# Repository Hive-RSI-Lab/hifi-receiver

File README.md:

# hifi-receiver-2

The WiiM-Ultra-like hi-fi streaming receiver/amp product in tiers (barebones, medium, full), designed with hwde on H0: boards, firmware, app, enclosure, manuals.

- [docs/product.md](docs/product.md): the three tiers (Lite, Plus, Ultra), every decision and why, power, cost and build order.
- [docs/plan.md](docs/plan.md): the later work in order, one worker session each.
- [docs/bom-estimate.csv](docs/bom-estimate.csv) + `python3 tools/bom_estimate.py`: per-tier BOM and JLC cost at 10 and 100 units (`--unit lite 100` prints one number).
- [docs/bom-stock.md](docs/bom-stock.md) + `python3 tools/bom_stock.py`: every board's BOM against live JLC and LCSC stock before an order, with checked alternates ([bom-alternates.csv](docs/bom-alternates.csv)) where a part is short.
- [docs/checks.md](docs/checks.md) + `python3 tools/hwcheck.py test|score`: the project's check (product.md complete, every board passes hwde's erc, drc_routed, verify and dfm gates) and score (the whole product, lower is better: every tier's unit cost at 100 from its boards' BOMs, counted only when they pass their gates and carry every function [`tools/product.json`](tools/product.json) names, plus 100 for each piece (firmware, app, bench, enclosures, manual) until its check in `tools/pieces.py`, which a stub fails, and its tests pass).
- [docs/order-readiness.md](docs/order-readiness.md): where each board stands before the order (gates, sims, reviews, firmware, bring-up plans) and what needs the person.
- [docs/manual/](docs/manual/user-manual.md): the user manual for all three tiers, the one-page [quick start](docs/manual/quick-start.md) for the box, and [sources.md](docs/manual/sources.md): where each fact comes from and what is still to be confirmed.
- [docs/app.md](docs/app.md) + `app/`: the web app (PWA) the firmware serves: what it does, the API it needs beyond docs/test-api.md, a mock receiver (`python3 app/mock/server.py`), the firmware pack (`python3 app/build.py`), tests (`python3 app/tests/test_app.py`) and screenshots.

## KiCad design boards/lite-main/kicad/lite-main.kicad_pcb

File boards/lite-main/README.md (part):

# lite-main: the Lite tier of hifi-receiver-2

The Lite tier's one board, as `docs/product.md` defines it. You plug a USB-C PD
laptop charger of 65 W or more and a pair of speakers into it (Lite asks for
20 V and uses at most what that contract allows, 60–65 W with an ordinary
cable: a bigger charger adds nothing; see issue #136). It streams over Wi-Fi
(Spotify Connect, AirPlay, Lyrion) and Bluetooth, takes a DJ deck on RCA, and
drives two subwoofers from RCA sub outs. A web app on your phone, three buttons
or any IR remote control it.

It was designed with the hive-hwde module (KiCad 10), from schematic to JLC fab
package, on 2026-10-28. **Nothing has been ordered.** Ordering and paying are
the person's. The workspace is named after the board, `boards/lite-main/` (the
brief said `boards/lite/`): that is the path `tools/hwcheck.py` scores, from
product.md's Boards row.

## What it is

- **Board:** 2 layers, 1.6 mm FR-4, 1 oz, OSP, 118 x 90 mm, four M3 holes
  (H1-H3 plated, H4 bare), 2 mm corners. 154 parts, all on the top side. 147 are SMT; 7 are
  through-hole (J2, J3, J4-J7 and U9). The 4 mounting holes are not BOM parts.
  JLC assembly with LCSC part numbers.
- **Rear edge, left to right:**
  - **J2:** RCA line in (FLX4). Top jack white = L, bottom red = R. ESD: D3/D4.
  - **J3:** RCA sub out L/R. ESD: D5/D6.
  - **J1:** USB-C.
  - **J4-J7:** the speaker outputs, four 4 mm banana sockets (Amass 24.243,
    right-angle PCB mount, 24 A, red C7437321 / black C7437322; JLC fits
    them): J4 L+, J5 L-, J6 R+, J7 R-, at 11 mm pitch. Their round collars
    (9.40 mm across, 2.60 mm long, bottom 3.20 mm over the board) reach 2.65 mm
    past the rear edge into the enclosure's 10.2 mm round holes, bore axis
    8.1 mm over the board. Body 10.10 mm wide, 10.70 mm across the rib; pins
    15.5 +/-0.3 mm (Multicomp's sheet for the same part numbers; Amass's says 15.7). Nothing is wired by hand. Single banana plugs;
    the 11 mm pitch is too close for a dual (19 mm) plug.
- **Front edge:** SW1 vol-, SW2 vol+, SW3 play/source (hold = BT pairing),
  the IR receiver U9 (an IRM-3638T standing at the edge with its lens facing
  forward through the front wall) and a red status LED D2.
- **ESP32 antenna:** at the left edge. A copper keep-out on both layers runs
  from 15 mm above it to the bottom edge, and no copper is left in the check's
  15 mm bands either side. H4, 8 mm below the antenna, is a bare unplated hole
  for that reason, so a metal screw there sits near the antenna with no ground
  bond (`docs/boards/lite-preorder.md`).

| Block | Parts | Notes |
|---|---|---|
| USB-C + PD | J1 HRO TYPE-C-31-M-12 (20 V/5 A), U1 CH224A, D1 SMBJ22A; ESD: D7/D8 PESDNC2FD5VB (D+/D-; CC exempt, docs/boards/lite-esd.md) | asks for 20 V (Rset 120k); I2C 0x22 on the codec's bus, so firmware reads the protocol status (0x09) and the PDO's max current (0x50). The CH224A has no SRCCAP registers (CH224Q only). |
| PVDD switch | Q1 AO4485, Q4 MMBT3904 | on only when GPIO18 is high **and** the PD contract is good (Q4's emitter is CH224A PG); C19 holds the gate shut on VBUS steps; soft start ~28 ms, 0.41 A inrush; R16 bleeder |
| 5 V | U2 TPS54302, L5 10 uH | TI design-example values |
| 3.3 V | U3 SY8089 (digital), U4 LP5907 (codec analog) | |
| MCU | U5 ESP32-WROVER-E-N8R8, U6 CH340B, Q2/Q3 | console + flashing over the same USB-C; auto-program on DTR/RTS |
| Codec | U7 ES8388 | pinned like the ESP32-A1S AudioKit (I2S MCLK 0, BCLK 27, LRCK 25, DOUT 26, DIN 35; I2C 32/33): squeezelite-esp32's board profile applies |
| Amp | U8 TPA3118D2, L1-L4 10 uH 8 A, C68-C71 1 uF | BTL, 26 dB, BD mode, no power limit; 2 x 38.7 W into 4 ohm at 20 V, 1 % THD (review-2) |
| Self-measurement | R66-R69, C81-C84 | SPK_L_P / SPK_R_P through 100k/10k, 470 pF, 1 uF into the codec's LIN2/RIN2: the board records its own speaker outputs (ratio 0.0625 with the ADC's input) |
| Bulk | C58 470 uF polymer, C59 220 uF | |

ESP32 pin map:

| GPIO | Signal |
|---|---|
| 0 | MCLK |
| 4 | PD power-good |
| 13 | vol+ |
| 14 | IR |
| 18 | PVDD enable |
| 19 | play |
| 21 | amp SDZ (through 100k) |
| 22 | LED |
| 23 | amp fault |
| 34 | VBUS/11 |
| 39 | PVDD/11 (firmware confirms the switch closed) |
| 36 | vol- |
| 1/3 | UART0, also on spare header J8 |
| 5, 15 | unused by the audio side, on spare header J8 (boot straps) |

The full table is in [`architecture/blocks.md`](architecture/blocks.md). Spare header J8:
[`docs/boards/lite-header.md`](../../docs/boards/lite-header.md).

## First-spin review (review-2, 2026-10-29)

Six independent reviewers (power, audio, digital/RF, thermal, DFM, parts
pin-to-pad) read this board from its KiCad files and the vendor datasheets:
[`docs/review-2/`](../../docs/review-2/). No pinout errors. What changed on
this board because of it:

| Finding | Was | Now |
|---|---|---|
| AUDIO-4 / DIGITAL-14 (major): the amp could stay in shutdown, since SDZ's up-to-50 uA input current through 100k left it under 2 V | R54 100k | R54 10k (SDZ >= 2.7 V) + C26 47 nF slew limit |
| POWER-3 (major): Q1 turned itself on at every VBUS step with the firmware off (C2 Miller coupling) | R6 47k | R6 220k + C19 4.7 uF gate-source (Vsg <= 6.6 V, so 16 V 0603) |
| POWER-4 (major): firmware turn-on at the AO4485 SOA edge, 2.5 A inrush on a 3 A contract | 6 ms ramp | 28 ms ramp, 0.41 A, 5.8 W peak (simulated, >3x SOA margin) |
| AUDIO-7: 1.5-2 dB line-in headroom at the FLX4's 2.1 Vrms | R30/R33 10k | 15k: -4.2 dBFS |
| POWER-10: 5 V buck crossover above TI's 40 kHz | C9 100 pF, 2 x 22 uF | C9 47 pF, + C25 22 uF |
| DFM-2: RCA pin rows ambiguous on the maker's drawing | round pin holes, 1.7 x 2.4 leg holes | pins 1/3 are 1.6 x 2.4 plated slots covering both readings; legs 2.0 x 3.0 as drawn |
| Stock: USB4105 0 free at JLC; CH340C not buyable | USB4105, CH340C | HRO TYPE-C-31-M-12 (20 V, Lite asks 20 V), CH340B |

THERMAL-3 (continuous full power trips the latched OTP) and AUDIO-6
(0 dBFS overdrives the amp by 4.1 dB) are firmware's:
[`docs/review-2/firmware-requirements.md`](../../docs/review-2/firmware-requirements.md).
Every fact the board relies on is in [`docs/known-unknowns.md`](../../docs/known-unknowns.md)
(`python3 tools/known_unknowns.py --check` before ordering).

The changes went in as an ECO on the routed board, keeping all other
copper: `kicad/gen/eco_swap.py` (J1/U6 swaps; J1's VBUS/GND pads made plain
0.6 mm rectangles and its signal pads trimmed to the USB4105's inner edge),
`eco_rca.py`, then `board_update` with `find_spots.py` placements, and the new
nets routed with `miniroute.py`/`add_track.py`/`add_via.py`. Freerouting timed
out twice on the routed board under the machine's load.

## Design decisions, and why

Each one is also in `state.json` (`decisions`). The schematic review and what
was done about each finding is in
[`reports/review-schematic-response.md`](reports/review-schematic-response.md).

- **CH224A, not the CH224Q product.md named.** Same die and registers. The
  CH224Q's 2 x 2 mm, 0.4 mm-pitch DFN puts VBUS between CC1 and CFG1, right
  under the USB-C, and it couldn't be fanned out on 2 layers. The ESSOP-10 is
  1.0 mm pitch, same price, 9.5k in stock. The CH224K has 1 in stock.
- **The CC lines are crossed on purpose.** The CH224 treats CC1/CC2 alike, so
  J1's B5 goes to U1 pin 7 and A5 to pin 6. That way neither crosses the
  other or the D+/D- escape.
- **Banana sockets on the board, not binding posts wired to a terminal**
  (task 261030-140102: the person orders, plugs in and does nothing else).
  Amass 24.243 is the only board-mount 4 mm socket JLC stocks (GC4010-F is a
  panel bullet connector). Four at 10.1 mm wide didn't fit the 100 mm edge
  beside USB-C and the RCA jacks, so the board grew to 118 mm east; H2 moved
  under the sockets to (114.45, 27). The L row moved 2.2 mm toward U8, and
  the 1 uF output caps (C68-C71) and R68 sit between the sockets' backs and
  the inductors. `kicad/gen/banana_route.py` is the speaker copper: L+ and R+
  on F.Cu, L- and R- through seven vias each (3.5 A) on B.Cu under the
  sockets. Both pins of each socket are its contact and carry the current.
- **Amp channels swapped at the chip.** The TPA3118's "right" channel drives
  the left speaker, so its output row runs L+ L- R+ R- straight into the
  terminal with no crossing. Nets are named by speaker channel.
- **PVDD needs firmware and the PD contract.** GPIO18 AND CH224A PG (hardware
  AND through Q4's emitter). A 5 V laptop port can never power the amp, and
  the firmware can drop it before a PD renegotiation.
- **5 V buck is a TPS54302**, not the SY8303 in the cost estimate: TI's
  datasheet design example gives every value. 5.18 V (100k/13k, Basic parts).
- **SMBJ22A TVS** (BORN C151920; standoff 22 V, breakdown 24.4–26.9 V,
  clamp 35.5 V at 16.9 A). PD allows 20 V +5 %, so the rail can sit at 21 V:
  the SMBJ20A first fitted had a 20 V standoff, under that, and hwde's USB-C
  PD sink rule asks for working >= 22 V. A 22 V part is the lowest standoff
  that holds 21 V; it still breaks down below the 30 V abs-max of the
  TPS54302 and TPA3118. Same SMB footprint, pin 1 = cathode. No TVS can
  hold a 21 V bus under 30 V at its full rated surge; that residual risk is
  review-2 POWER-9 (PD attaches at 5 V, so real surge energy is small).
- **J1 is rated 20 V, waived at 21 V.** The HRO TYPE-C-31-M-12 drawing gives
  "VOLTAGE RATING: 20V", the standard Type-C class for 20 V PD; hwde checks it
  against the 21 V top of PD tolerance. Kept the part and the 20 V contract
  (15 V costs amp power; a 48 V EPR receptacle is a copper change) with a
  waiver in `reports/verify-waivers.json` (issue #181).
- **TPA3118 gain 26 dB.** The ES8388's full scale (~0.9 Vrms) x 20 clips at
  20 V into 4 ohm 3.7 dB before 0 dBFS, so firmware caps the codec volume.
  20 dB would leave only 20 W.
- **Power copper is pours, not tracks.** VBUS (J1 to Q1) and PVDD carry up
  to 5 A, joined by 16 vias. PVDD runs from Q1's drain down a B.Cu column
  under the filter caps, so the speaker lines cross it on F.Cu. It continues
  as a B.Cu pour under the inductors, stopping 5 mm short of the amp so the
  ground under it is unbroken, then F.Cu islands at both PVCC groups. The pours
  are in `kicad/gen/power.py`. Tracks only feed the small taps.
- **Amp OUT runs (pin to inductor) are 0.31 mm minimum** at the HTSSOP pins
  (0.65 mm pitch, 0.34 mm pins), sized for 1.0 A rms / 30 C. That is music at
  full power with a 9 dB crest factor. They are under 15 mm long. The
  inductor-to-socket runs are 1.25 mm (3.5 A, 30 C).
- **USB is not impedance-controlled.** Full speed, 12 Mb/s; a 90 ohm pair on
  1.6 mm 2-layer would be 1.1 mm wide.
- **USB ESD:** D7/D8 (PESDNC2FD5VB) are fitted on D+/D-; the CC pins have no
  clamp (docs/boards/lite-esd.md).
- **Board 118 x 90 mm**, not the ~100 x 80 product.md estimated: 80 left no
  room for the PVDD switch between USB-C and the amp, and the banana sockets
  took 18 mm more.
- **Red LED (Basic part) at 1.3 mm.** The white one the first schematic had ran
  at 0.2-0.6 mA, too dim.
- **IR on GPIO14**, not 39: GPIO36/39 glitch with ADC/Wi-Fi (errata 3.11).
  vol- stays on 36; a polled, debounced button tolerates the glitch. GPIO39
  reads PVDD/11 instead (firmware worker's ask), which is sampled, not edge-triggered.
- **Front-facing IR receiver.** The enclosure worker found the top-looking
  IRM-H638T would sit 31 mm under the lid, outside a remote's 45 degree cone.
  It is now a through-hole IRM-3638T whose lens faces through the front wall,
  with Everlight's 100 ohm / 4.7 uF supply filter.

## The checks it passed

The pre-order round of 2026-11-01 (hwde 0600487: vias off pads, I2S respaced, VBUS stubs, box holes) is in `docs/boards/lite-preorder.md`.

| Gate | Result |
|---|---|
| ERC (`erc`) | 0 errors, 0 warnings (every pulled pin is typed passive, so the schematic review checked pins by hand) |
| Placement (`place`) | pass, 0 errors |
| Routed DRC (`drc_routed`) | 0 errors, 0 warnings, 0 unconnected |
| Verify suite (`verify`) | pass, with one signed waiver (U8 thermal, below) and 44 warnings, now shown by hwde e225475: 25 route-style (off-45 jogs in Freerouting and maze-router copper; DRC-clean, cosmetic), 18 part ratings with no datasheet extraction (each part's voltage and current margin is in `docs/review-2/` instead), 1 decoupler 5.3 mm from U8 pin 31 (C57, 1 nF HF cap, limit 5.0; 0.3 mm over, left) |
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
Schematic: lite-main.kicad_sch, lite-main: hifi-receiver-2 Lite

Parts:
C1, C15, C16, C22, C41, C44, C50, C60, C61, C62, C63, C82, C84: 1uF; C_0603_1608Metric; LCSC C15849
C2, C5, C6, C11, C17, C18, C21, C23, C24, C30, C31, C33, C34, C36, C38, C40, C53, C56: 100nF; C_0603_1608Metric; LCSC C14663
C3: 10uF; C_1206_3216Metric; LCSC C13585
C4: 4.7uF; C_1206_3216Metric; LCSC C29823
C7, C8, C12, C25, C90: 22uF; C_0805_2012Metric; LCSC C45783
C9: 47pF; C_0603_1608Metric; LCSC C1671
C10, C13, C20, C35, C37, C39, C47, C48: 10uF; C_0603_1608Metric; LCSC C19702
C14: 22pF; C_0603_1608Metric; LCSC C1653
C19, C32, C80: 4.7uF; C_0603_1608Metric; LCSC C19666
C26: 47nF; C_0603_1608Metric; LCSC C1622
C42, C45: 100pF; C_0603_1608Metric; LCSC C14858
C51, C52, C55: 1uF; C_0805_2012Metric; LCSC C28323
C54, C57: 1nF; C_0603_1608Metric; LCSC C1588
C58: 470uF 35V polymer; CAP-SMD_BD10.0-L10.3-W10.3-FD-LS11.0; LCSC C46550472
C59: 220uF 35V; CAP-SMD_BD8.0-L8.3-W8.3-LS9.3-FD; LCSC C2836441
C64, C65, C66, C67: 220nF; C_0603_1608Metric; LCSC C21120
C68, C69, C70, C71: 1uF; C_1206_3216Metric; LCSC C1848
C81, C83: 470pF; C_0603_1608Metric; LCSC C1620
D1: SMBJ22A; SMB_L4.6-W3.6-LS5.3-RD; LCSC C151920
D2: red; LED-SMD_L1.6-W0.8-R-RD; LCSC C2286
D3, D4, D5, D6, D7, D8: PESDNC2FD5VB; DFN1006-2L-BI; LCSC C110694
J1: TYPE-C-31-M-12; USB-C_SMD-TYPE-C-31-M-12_1; LCSC C165948
J2: RCA line in; CONN-TH_XDJK-0271-1650; LCSC C7527522
J3: RCA sub out; CONN-TH_XDJK-0271-1650; LCSC C7527522
J4, J6: 24.243 red; CONN-TH_24.243.1_RED; LCSC C7437321
J5, J7: 24.243 black; CONN-TH_24.243.2; LCSC C7437322
L1, L2, L3, L4: 10uH 8A; IND-SMD_L8.0-W8.0_XR0850; LCSC C48391614
L5: 10uH; IND-SMD_L6.0-W6.0_SWPA6045S; LCSC C79272
L6: 2.2uH; IND-SMD_L4.0-W4.0_VLCF4020; LCSC C305171
Q1: AO4485; SOP-8_L4.9-W3.9-P1.27-LS6.0-BL; LCSC C5125949
Q2, Q3, Q4, Q11, Q12: MMBT3904; SOT-23-3_L2.9-W1.3-P1.90-LS2.4-BR; LCSC C20526
Q13, Q14, Q15: 2N7002; SOT-23-3_L2.9-W1.3-P1.90-LS2.4-BR; LCSC C8545
R1, R80: 120k; R_0603_1608Metric; LCSC C25808
R2, R3: 0R; R_0603_1608Metric; LCSC C21189
R4, R7, R14, R18, R20, R21, R24, R25, R31, R34, R53, R54, R60, R61, R62, R63, R67, R69: 10k; R_0603_1608Metric; LCSC C25804
R5, R8, R9, R13, R17, R51, R52, R66, R68: 100k; R_0603_1608Metric; LCSC C25803
R6: 220k; R_0603_1608Metric; LCSC C22961
R10: 13k; R_0603_1608Metric; LCSC C22797
R11: 150k; R_0603_1608Metric; LCSC C22807
R12: 33k; R_0603_1608Metric; LCSC C4216
R15, R36, R38, R64: 1k; R_0603_1608Metric; LCSC C21190
R16, R81: 22k; R_0603_1608Metric; LCSC C31850
R22, R23: 2.2k; R_0603_1608Metric; LCSC C4190
R30, R33: 15k; R_0603_1608Metric; LCSC C22809
R37, R39, R82: 47k; R_0603_1608Metric; LCSC C25819
R50: 20k; R_0603_1608Metric; LCSC C4184
R65: 100R; R_0603_1608Metric; LCSC C22775
SW1, SW2, SW3: TS-1187A; SW-SMD_4P-L5.1-W5.1-P3.70-LS6.5-TL_H1.5; LCSC C318884
U1: CH224A; ESSOP-10_L4.9-W3.9-P1.0-LS6.0-TL-EP; LCSC C42459160
U2: TPS54302; SOT-23-6_L2.9-W1.6-P0.95-LS2.8-BL; LCSC C311983
U3: SY8089A1AAC; TSOT-23-5_L2.9-W1.6-P0.95-LS2.8-BR; LCSC C479074
U4: LP5907-3.3; SOT-23-5_L3.0-W1.7-P0.95-LS2.8-BR; LCSC C80670
U5: ESP32-WROVER-E-N8R8; WIFI-SMD_ESP32-WROVER-IE8MB; LCSC C2973667
U6: CH340B; SOP-16_L10.0-W3.9-P1.27-LS6.0-BL; LCSC C81010
U7: ES8388; QFN-28_L4.0-W4.0-P0.45-BL-EP; LCSC C365736
U8: TPA3118D2; HTSSOP-32_L11.0-W6.1-P0.65-LS8.1-BL-EP; LCSC C46497
U9: IRM-3638T; OPTO-TH_IRM-3638T; LCSC C42421366

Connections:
+3V3: C12.1, C13.1, C14.1, C20.1, C21.1, C23.1, C24.1, C30.1, C31.1, L6.2, R4.2, R11.1, R20.1, R21.1, R22.1, R23.1, R53.1, R60.1, R61.1, R62.1, R63.1, R65.1, U5.2 (3V3), U6.4 (V3), U6.16 (VCC), U7.2 (DVDD), U7.3 (PVDD); also elsewhere on the board
+3V3A: C16.1, C32.1, C33.1, C34.1, U4.5 (OUT), U7.16 (HPVDD), U7.17 (AVDD)
+5V: C7.1, C8.1, C9.1, C10.1, C11.1, C15.1, C25.1, L5.2, Q11.1 (B), Q11.3 (C), R9.1, R80.1, U3.1 (EN), U3.4 (IN), U4.1 (IN), U4.3 (EN)
/AMP_FAULTZ: R53.2, U5.37 (IO23), U8.3 (FAULTZ)
/AMP_GAIN: R50.1, R51.2, U8.8 (GAIN/SLV)
/AMP_GVDD: C50.1, R51.1, U8.6 (PLIMIT), U8.7 (GVDD)
/AMP_IN_L: C60.1, U7.12 (LOUT1)
/AMP_IN_R: C62.1, U7.11 (ROUT1)
/AMP_L_INN: C61.1, U8.5 (RINN)
/AMP_L_INP: C60.2, U8.4 (RINP)
/AMP_R_INN: C63.1, U8.11 (LINN)
/AMP_R_INP: C62.2, U8.10 (LINP)
/AMP_SDZ: C26.1, R54.2, U8.2 (SDZ)
/AMP_SDZ_IO: R52.1, R54.1, U5.33 (IO21)
/BS_L_N: C65.1, U8.26 (BSNR)
/BS_L_P: C64.1, U8.30 (BSPR)
/BS_R_N: C67.1, U8.20 (BSNL)
/BS_R_P: C66.1, U8.24 (BSPL)
/BTN_PLAY: R62.2, SW3.1 (A), SW3.2 (B), U5.31 (IO19)
/BTN_VOLDN: R60.2, SW1.1 (A), SW1.2 (B), U5.4 (SENSOR_VP)
/BTN_VOLUP: R61.2, SW2.1 (A), SW2.2 (B), U5.16 (IO13)
/BUCK3_FB: C14.2, R11.2, R12.1, U3.5 (FB)
/BUCK3_LX: L6.1, U3.3 (LX)
/BUCK5_BST: C6.1, U2.6 (BOOT)
/BUCK5_FB: C9.2, R9.2, R10.1, U2.4 (FB)
/BUCK5_SW: C6.2, L5.1, U2.2 (SW)
/CC1: J1.A5 (CC1), U1.6 (CC2)
/CC2: J1.B5 (CC2), U1.7 (CC1)
/CODEC_DACVREF: C37.1, C38.1, U7.19 (ADCVREF)
/CODEC_VMID: C39.1, C40.1, U7.20 (VMID)
/CODEC_VREF: C35.1, C36.1, U7.10 (VREF)
/DTR: Q3.2 (E), R24.1, U6.13 (~DTR)
/ESP_EN: C22.1, Q2.3 (C), R20.2, U5.3 (EN)
/GPIO5: U5.29 (IO5); also elsewhere on the board
/GPIO15: U5.23 (IO15); also elsewhere on the board
/I2C_SCL: R2.2, R22.2, U5.8 (IO32), U7.28 (CCLK); also elsewhere on the board
/I2C_SDA: R3.2, R23.2, U5.9 (IO33), U7.27 (CDATA); also elsewhere on the board
/I2S_BCLK: U5.12 (IO27), U7.5 (SCLK)
/I2S_DIN: U5.7 (IO35), U7.8 (ASDOUT)
/I2S_DOUT: U5.11 (IO26), U7.6 (DSDIN)
/I2S_LRCK: U5.10 (IO25), U7.7 (LRCK)
/I2S_MCLK: Q3.3 (C), R21.2, U5.25 (IO0), U7.1 (MCLK)
/IR_IN: R63.2, U5.13 (IO14), U9.1 (OUT)
/LED_A: D2.1 (A), R64.2
/LED_DRV: R64.1, U5.36 (IO22)
/LINEIN_L: C42.1, D3.1, J2.1, R30.1
/LINEIN_L_C: C41.2, U7.24 (LIN1)
/LINEIN_L_D: C41.1, R30.2, R31.1
/LINEIN_R: C45.1, D4.1, J2.3, R33.1
/LINEIN_R_C: C44.2, U7.23 (RIN1)
/LINEIN_R_D: C44.1, R33.2, R34.1
/MUTE_DET: Q12.1 (B), R80.2, R81.1
/MUTE_RES: C90.1, Q11.2 (E), R82.1
/MUTE_S: Q13.2 (S), Q14.2 (S), Q15.2 (S)
/OUT_L_N: C65.2, L2.1, U8.27 (OUTNR)
/OUT_L_P: C64.2, L1.1, U8.29 (OUTPR)
/OUT_R_N: C67.2, L4.1, U8.21 (OUTNL)
/OUT_R_P: C66.2, L3.1, U8.23 (OUTPL)
/PD_CFG1: R1.1, U1.9 (CFG1)
/PD_PG: Q4.2 (E), R4.1, U1.10 (PG), U5.26 (IO4)
/PD_SCL: R2.1, U1.2 (CFG2/SCL)
/PD_SDA: R3.1, U1.3 (CFG3/SDA)
/PSW_B: Q4.1 (B), R7.2
/PSW_G: C19.2, Q1.4 (G), R5.2, R6.1, R15.1
/PSW_MILLER: C2.1, R15.2
/PSW_PULL: Q4.3 (C), R6.2
/PVDD_EN: R7.1, R8.1, U5.30 (IO18)
/PVDD_SENSE: C18.1, R17.2, R18.1, U5.5 (SENSOR_VN)
/Q2_B: Q2.1 (B), R24.2
/Q3_B: Q3.1 (B), R25.2
/RTS: Q2.2 (E), R25.1, U6.14 (~RTS)
/SPK_L_N: C69.1, J5.1, J5.2, L2.2
/SPK_L_P: C68.1, J4.1, J4.2, L1.2, R66.1
/SPK_R_N: C71.1, J7.1, J7.2, L4.2
/SPK_R_P: C70.1, J6.1, J6.2, L3.2, R68.1
/SUB_L: D5.1, J3.1, Q13.3 (D), R36.2, R37.1
/SUB_L_AC: C47.2, R36.1
/SUB_L_RAW: C47.1, U7.15 (LOUT2)
/SUB_MUTE: Q12.3 (C), Q13.1 (G), Q14.1 (G), Q15.1 (G), R82.2
/SUB_R: D6.1, J3.3, Q15.3 (D), R38.2, R39.1
/SUB_R_AC: C48.2, R38.1
/SUB_R_RAW: C48.1, U7.14 (ROUT2)
/TAP_L: C81.1, C82.1, R66.2, R67.1
/TAP_L_C: C82.2, U7.22 (LIN2)
/TAP_R: C83.1, C84.1, R68.2, R69.1
/TAP_R_C: C84.2, U7.21 (RIN2)
/U0RXD: U5.34 (RXD0), U6.2 (TXD); also elsewhere on the board
/U0TXD: U5.35 (TXD0), U6.3 (RXD); also elsewhere on the board
/USB_DM: D8.1, J1.A7 (DN1), J1.B7 (DN2), U6.6 (UD-)
/USB_DP: D7.1, J1.A6 (DP1), J1.B6 (DP2), U6.5 (UD+)
/VBUS_SENSE: C17.1, R13.2, R14.1, U5.6 (IO34)
GND: C1.2, C3.2, C4.2, C5.2, C7.2, C8.2, C10.2, C11.2, C12.2, C13.2, C15.2, C16.2, C17.2, C18.2, C20.2, C21.2, C22.2, C23.2, C24.2, C25.2, C26.2, C30.2, C31.2, C32.2, C33.2, C34.2, C35.2, C36.2, C37.2, C38.2, C39.2, C40.2, C42.2, C45.2, C50.2, C51.2, C52.2, C53.2, C54.2, C55.2, C56.2, C57.2, C58.2, C59.2, C61.2, C63.2, C68.2, C69.2, C70.2, C71.2, C80.2, C81.2, C83.2, C90.2, D1.2 (A), D2.2 (K), D3.2, D4.2, D5.2, D6.2, D7.2, D8.2, J1.1 (EH), J1.2 (EH), J1.3 (EH), J1.4 (EH), J1.A1B12 (GND), J1.B1A12 (GND), J2.2, J3.2, Q12.2 (E), Q14.3 (D), R1.2, R8.2, R10.2, R12.2, R14.2, R16.2, R18.2, R31.2, R34.2, R37.2, R39.2, R50.2, R52.2, R67.2, R69.2, R81.2, SW1.3 (C), SW1.4 (D), SW2.3 (C), SW2.4 (D), SW3.3 (C), SW3.4 (D), U1.11 (GND), U2.1 (GND), U3.2 (GND), U4.2 (GND), U5.1 (GND), U5.15 (GND), U5.38 (GND), U5.39 (GND), U6.1 (GND), U7.4 (DGND), U7.13 (HPGND), U7.18 (AGND), U7.26 (CE), U7.29 (EP), U8.1 (MODSEL), U8.9 (GND), U8.12 (MUTE), U8.13 (AM2), U8.14 (AM1), U8.15 (AM0), U8.22 (GND), U8.25 (GND), U8.28 (GND), U8.33 (EP), U9.2 (GND); also elsewhere on the board
IR_VCC: C80.1, R65.2, U9.3 (VCC)
PVDD: C2.2, C51.1, C52.1, C53.1, C54.1, C55.1, C56.1, C57.1, C58.1, C59.1, Q1.5 (D), Q1.6 (D), Q1.7 (D), Q1.8 (D), R16.1, R17.1, U8.17 (AVCC), U8.18 (PVCC), U8.19 (PVCC), U8.31 (PVCC), U8.32 (PVCC)
VBUS: C1.1, C3.1, C4.1, C5.1, C19.1, D1.1 (K), J1.A4B9 (VBUS), J1.B4A9 (VBUS), Q1.1 (S), Q1.2 (S), Q1.3 (S), R5.1, R13.1, U1.1 (VHV), U1.8 (VBUS), U2.3 (VIN)

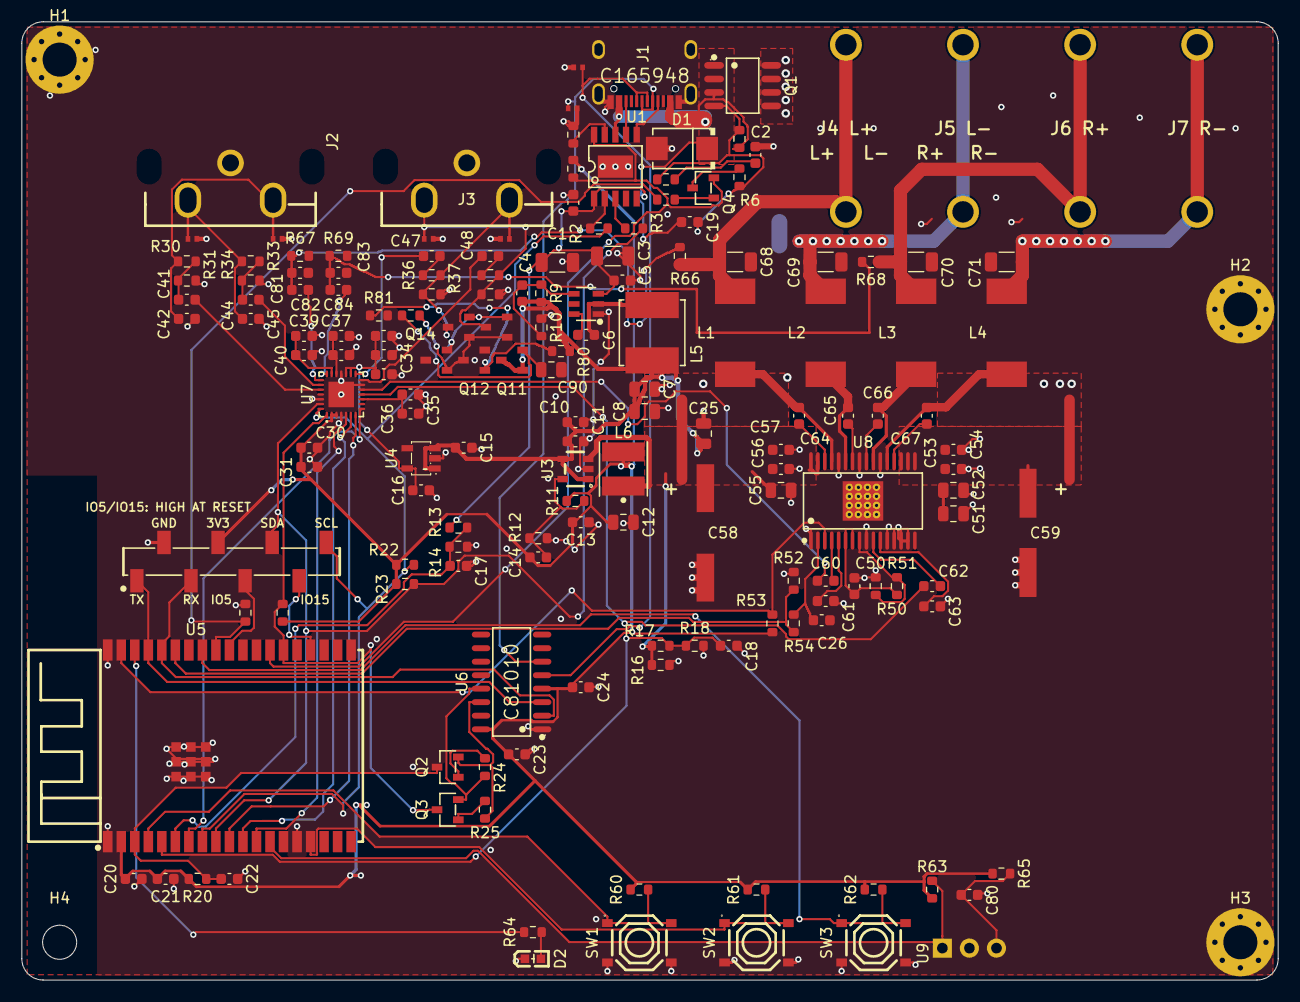
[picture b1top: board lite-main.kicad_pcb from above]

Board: 2 copper layers, 118.0 x 90.0 mm, 168 parts (0 on the bottom side), 95 nets.

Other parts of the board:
H1, H2, H3: MountingHole_3.2mm_M3_Pad_Via
H4: MountingHole_3.2mm_M3
J8: ESP32 spare header; HDR-SMD_8P-P2.54-V-M-LS4.8_R2

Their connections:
+3V3: J8.4; also elsewhere on the board
/GPIO5: J8.5; also elsewhere on the board
/GPIO15: J8.7; also elsewhere on the board
/I2C_SCL: J8.8; also elsewhere on the board
/I2C_SDA: J8.6; also elsewhere on the board
/U0RXD: J8.3; also elsewhere on the board
/U0TXD: J8.1; also elsewhere on the board
GND: H1.1, H2.1, H3.1, J8.2; also elsewhere on the board

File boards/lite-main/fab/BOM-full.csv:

Comment,Designator,Qty Per Board,Footprint,MPN,LCSC,Assembly Class,Instructions
1uF,"C1,C15,C16,C22,C41,C44,C50,C60,C61,C62,C63,C82,C84",13,C_0603_1608Metric,CL10A105KB8NNNC,C15849,smt_placed,
100nF,"C2,C5,C6,C11,C17,C18,C21,C23,C24,C30,C31,C33,C34,C36,C38,C40,C53,C56",18,C_0603_1608Metric,CC0603KRX7R9BB104,C14663,smt_placed,
10uF,C3,1,C_1206_3216Metric,CL31A106KBHNNNE,C13585,smt_placed,
4.7uF,C4,1,C_1206_3216Metric,1206B475K500NT,C29823,smt_placed,
22uF,"C7,C8,C12,C25,C90",5,C_0805_2012Metric,CL21A226MAQNNNE,C45783,smt_placed,
47pF,C9,1,C_0603_1608Metric,CL10C470JB8NNNC,C1671,smt_placed,
10uF,"C10,C13,C20,C35,C37,C39,C47,C48",8,C_0603_1608Metric,CL10A106KP8NNNC,C19702,smt_placed,
22pF,C14,1,C_0603_1608Metric,CL10C220JB8NNNC,C1653,smt_placed,
4.7uF,"C19,C32,C80",3,C_0603_1608Metric,CL10A475KO8NNNC,C19666,smt_placed,
47nF,C26,1,C_0603_1608Metric,CL10B473KB8NNNC,C1622,smt_placed,
100pF,"C42,C45",2,C_0603_1608Metric,CL10C101JB8NNNC,C14858,smt_placed,
1uF,"C51,C52,C55",3,C_0805_2012Metric,CL21B105KBFNNNE,C28323,smt_placed,
1nF,"C54,C57",2,C_0603_1608Metric,CL10B102KB8NNNC,C1588,smt_placed,
470uF 35V polymer,C58,1,CAP-SMD_BD10.0-L10.3-W10.3-FD-LS11.0,MA35V470M10X13,C46550472,smt_placed,
220uF 35V,C59,1,CAP-SMD_BD8.0-L8.3-W8.3-LS9.3-FD,RVT220UF35V67RV0024,C2836441,smt_placed,
220nF,"C64,C65,C66,C67",4,C_0603_1608Metric,CL10B224KA8NNNC,C21120,smt_placed,
1uF,"C68,C69,C70,C71",4,C_1206_3216Metric,CL31B105KBHNNNE,C1848,smt_placed,
470pF,"C81,C83",2,C_0603_1608Metric,0603B471K500NT,C1620,smt_placed,
SMBJ22A,D1,1,SMB_L4.6-W3.6-LS5.3-RD,SMBJ22A,C151920,smt_placed,
red,D2,1,LED-SMD_L1.6-W0.8-R-RD,KT-0603R,C2286,smt_placed,
PESDNC2FD5VB,"D3,D4,D5,D6,D7,D8",6,DFN1006-2L-BI,PESDNC2FD5VB,C110694,smt_placed,
TYPE-C-31-M-12,J1,1,USB-C_SMD-TYPE-C-31-M-12_1,TYPE-C-31-M-12,C165948,smt_placed,
ESP32 spare header,J8,1,HDR-SMD_8P-P2.54-V-M-LS4.8_R2,X6511WVS-08H-C60D48R2,C2883765,smt_placed,
10uH 8A,"L1,L2,L3,L4",4,IND-SMD_L8.0-W8.0_XR0850,XR0850-100M,C48391614,smt_placed,
10uH,L5,1,IND-SMD_L6.0-W6.0_SWPA6045S,SWPA6045S100MT,C79272,smt_placed,
2.2uH,L6,1,IND-SMD_L4.0-W4.0_VLCF4020,SWPA4020S2R2NT,C305171,smt_placed,
AO4485,Q1,1,SOP-8_L4.9-W3.9-P1.27-LS6.0-BL,AO4485,C5125949,smt_placed,
MMBT3904,"Q2,Q3,Q4,Q11,Q12",5,SOT-23-3_L2.9-W1.3-P1.90-LS2.4-BR,MMBT3904(RANGE:100-300),C20526,smt_placed,
2N7002,"Q13,Q14,Q15",3,SOT-23-3_L2.9-W1.3-P1.90-LS2.4-BR,2N7002,C8545,smt_placed,
120k,"R1,R80",2,R_0603_1608Metric,0603WAF1203T5E,C25808,smt_placed,
0R,"R2,R3",2,R_0603_1608Metric,0603WAF0000T5E,C21189,smt_placed,
10k,"R4,R7,R14,R18,R20,R21,R24,R25,R31,R34,R53,R54,R60,R61,R62,R63,R67,R69",18,R_0603_1608Metric,0603WAF1002T5E,C25804,smt_placed,
100k,"R5,R8,R9,R13,R17,R51,R52,R66,R68",9,R_0603_1608Metric,0603WAF1003T5E,C25803,smt_placed,
220k,R6,1,R_0603_1608Metric,0603WAF2203T5E,C22961,smt_placed,
13k,R10,1,R_0603_1608Metric,0603WAF1302T5E,C22797,smt_placed,
150k,R11,1,R_0603_1608Metric,0603WAF1503T5E,C22807,smt_placed,
33k,R12,1,R_0603_1608Metric,0603WAF3302T5E,C4216,smt_placed,
1k,"R15,R36,R38,R64",4,R_0603_1608Metric,0603WAF1001T5E,C21190,smt_placed,
22k,"R16,R81",2,R_0603_1608Metric,0603WAF2202T5E,C31850,smt_placed,
2.2k,"R22,R23",2,R_0603_1608Metric,0603WAF2201T5E,C4190,smt_placed,
15k,"R30,R33",2,R_0603_1608Metric,0603WAF1502T5E,C22809,smt_placed,
47k,"R37,R39,R82",3,R_0603_1608Metric,0603WAF4702T5E,C25819,smt_placed,
20k,R50,1,R_0603_1608Metric,0603WAF2002T5E,C4184,smt_placed,
100R,R65,1,R_0603_1608Metric,0603WAF1000T5E,C22775,smt_placed,
TS-1187A,"SW1,SW2,SW3",3,SW-SMD_4P-L5.1-W5.1-P3.70-LS6.5-TL_H1.5,TS-1187A-B-A-B,C318884,smt_placed,
CH224A,U1,1,ESSOP-10_L4.9-W3.9-P1.0-LS6.0-TL-EP,CH224A,C42459160,smt_placed,
TPS54302,U2,1,SOT-23-6_L2.9-W1.6-P0.95-LS2.8-BL,TPS54302DDCR,C311983,smt_placed,
SY8089A1AAC,U3,1,TSOT-23-5_L2.9-W1.6-P0.95-LS2.8-BR,SY8089A1AAC,C479074,smt_placed,
LP5907-3.3,U4,1,SOT-23-5_L3.0-W1.7-P0.95-LS2.8-BR,LP5907MFX-3.3/NOPB,C80670,smt_placed,
ESP32-WROVER-E-N8R8,U5,1,WIFI-SMD_ESP32-WROVER-IE8MB,ESP32-WROVER-E-N8R8,C2973667,smt_placed,
CH340B,U6,1,SOP-16_L10.0-W3.9-P1.27-LS6.0-BL,CH340B,C81010,smt_placed,
ES8388,U7,1,QFN-28_L4.0-W4.0-P0.45-BL-EP,ES8388,C365736,smt_placed,
TPA3118D2,U8,1,HTSSOP-32_L11.0-W6.1-P0.65-LS8.1-BL-EP,TPA3118D2DAPR,C46497,smt_placed,
RCA line in,J2,1,CONN-TH_XDJK-0271-1650,XDJK-0271-1650,C7527522,tht,Through-hole - JLC THT assembly (or hand-solder after reflow); not on the SMT line.
RCA sub out,J3,1,CONN-TH_XDJK-0271-1650,XDJK-0271-1650,C7527522,tht,Through-hole - JLC THT assembly (or hand-solder after reflow); not on the SMT line.
24.243 red,"J4,J6",2,CONN-TH_24.243.1_RED,24.243.1,C7437321,tht,Through-hole - JLC THT assembly (or hand-solder after reflow); not on the SMT line.
24.243 black,"J5,J7",2,CONN-TH_24.243.2,24.243.2,C7437322,tht,Through-hole - JLC THT assembly (or hand-solder after reflow); not on the SMT line.
IRM-3638T,U9,1,OPTO-TH_IRM-3638T,IRM-3638T,C42421366,tht,Through-hole - JLC THT assembly (or hand-solder after reflow); not on the SMT line.
,"H1,H2,H3,H4",4,,,,board_feature,Realised in copper - nothing to buy or place.

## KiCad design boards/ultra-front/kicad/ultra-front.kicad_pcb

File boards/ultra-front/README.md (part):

# ultra-front

The front panel of the hifi-receiver-2 **Ultra** tier (see `docs/product.md`):
a 2-layer 110 x 40 mm board carrying the 2.0" colour screen, the volume knob,
three buttons, the IR remote receiver and an RGB status LED. It has no
processor: the `core` board's ESP32 drives everything over one 20-pin FFC
cable. Designed with the hive-hwde module on 2026-10-28, from schematic
through routed layout to a JLC fab package. **Nothing has been ordered;
ordering is the person's.**

## What it is

- 2 layers, 1.6 mm FR-4, 1 oz, **order ENIG** (HASL is uneven on J1's
  0.3 mm pads at 0.5 mm pitch; R5-UF-6), 110 x 40 mm, 2 mm corner radius,
  4 x M2.5 plated mounting holes (GND) 3.05 mm in from each corner.
- Everything is on the top side, which faces the user. All parts are SMD
  except the knob (EC11, through-hole).
- GND is poured on both layers, plus routed GND tracks and a via at each cap/IC GND pad.

| Ref | What | Part | LCSC | JLC |
|---|---|---|---|---|
| J1 | 20-pin 0.5 mm FFC socket to the core board | FPC-05F-20PH20 (bottom contact) | C2856803 | Extended |
| J2 | 12-pin 0.5 mm FPC socket for the LCD tail | FPC-05FB-12PH20 (contacts top and bottom) | C2856829 | Extended |
| U1 | 16-bit I2C GPIO expander, address 0x27 | TCA9535PWR (UMW) | C22396388 | Extended |
| U2 | 38 kHz IR remote receiver | IRM-H638T/TR2 | C91447 | Extended |
| SW4 | Rotary encoder with push switch (smooth, no detents) | EC11E1834403 | C361165 | Extended |
| SW1-SW3 | 5.1 mm tact switches | TS-1187A-B-A-B | C318884 | Basic |
| D1 | RGB status LED, common anode | TJ-S1615SW6TGLCCYRGB-A5 | C273610 | Extended |
| D2-D3 | ESD clamps at the switches, dual bidirectional 5 V (D2: BTN1/BTN2, D3: BTN3/ENC_SW) | PESD5V0S2BT,215 | C49338 | Extended |
| Q1 | Backlight switch | AO3400A | C20917 | Basic |
| R/C | 19 resistors, 7 capacitors, 0603/0805 | see `fab/BOM.csv` | | Basic |

Not on the board, and not assembled by JLC:

- **The LCD:** HS20HS072RX, 2.0" 320x240 IPS, ST7789, LCSC C5329582,
  $2.43 at 100. Its 12-pin tail plugs into J2, and the panel is taped to
  the board at final assembly.
- **The FFC cable to the core board:** 20-pin, 0.5 mm pitch. Its length and
  type are set by the enclosure: 50 mm, **type B (reverse / opposite-side
  contacts)**; a type A cable shorts core outputs to GND (enclosure/README.md,
  "The FFC").

**Parts cost:** $2.97 per board at 10 and $2.54 at 100, plus the LCD. It has
7 extended parts.

## The connector to the core board (J1)

Pin N on the core board connects to pin N here.

| Pin | Signal | Pin | Signal |
|---|---|---|---|
| 1 | GND | 11 | GND |
| 2 | +3V3 | 12 | I2C_SCL |
| 3 | +5V | 13 | I2C_SDA |
| 4 | GND | 14 | FRONT_INT_N (U1 INT, open-drain, 10 k pull-up here) |
| 5 | LCD_SCK | 15 | IR_OUT (active low, 10 k pull-up here) |
| 6 | GND | 16 | ENC_A (10 k pull-up + 10 nF here) |
| 7 | LCD_MOSI | 17 | ENC_B (10 k pull-up + 10 nF here) |
| 8 | LCD_CS | 18 | +5V |
| 9 | LCD_DC | 19 | +3V3 |
| 10 | LCD_BL_PWM (100 k pull-down here: backlight off until driven) | 20 | GND |

- **The rails are mirror-symmetric** (1/20, 2/19, 3/18). Whether pin 1 lands
  on pin 1 or pin 20 depends on the FFC type, same-side or opposite-side
  contacts. A wrong cable therefore never shorts a rail, but three signals
  would fight: the core's BL_PWM would meet GND, SCK would meet ENC_A and
  MOSI would meet INT. **The cable must map pin N to pin N.**
- **The cable:** 20-pin, 0.5 mm, 30-50 mm, **type B** (opposite-side
  contacts).
  - **Why type B:** in the Ultra enclosure the cable leaves the core's J3
    contacts-down, runs forward under this board and turns up into J1. Both
    ends are the bottom-contact FPC-05F-20PH20 (C2856803), the same part on
    both boards. A type-B cable then meets pin N to pin N without twisting.
  - **Source:** the enclosure task's `enclosure/README.md`. The core
    board's J3, as merged, carries this same pinout.
- **LCD_CS (pin 8):** the core holds it low with a 10 k resistor (its R57)
  rather than driving it. The LCD is the only device on that SPI bus, and
  the ST7789 runs with CS held low; firmware uses cs = -1.
- **Power drawn:** +3V3 about 30 mA, +5V about 70 mA, of which the
  backlight is about 50 mA.
- **What the core gives up:** 4 SPI outputs (SCK, MOSI, CS, DC), one PWM
  output for the backlight, 2 inputs (INT, IR; input-only GPIO34-39 is
  fine) and the shared I2C bus.
  - ENC_A/ENC_B are optional: wire them to 2 GPIOs for hardware quadrature
    (PCNT), or leave them unconnected and read the knob through U1.
  - I2C pull-ups are on the core, not here.
  - Put 22-33 R series resistors on SCK/MOSI at the ESP32.
  - Run SPI at 15 MHz or less: the LCD's minimum write clock period is 66 ns.
  - Keep these nets off ESP32 strapping pins (GPIO0/2/5/12/15), because this
    board biases them at boot.

## Design decisions, and why

- **An I2C expander (U1) reads the knob and buttons and drives the LED and
  LCD reset.** The core's ESP32-WROVER-E already gives its pins to Ethernet,
  two I2S buses and I2C, so the front board must cost it as few GPIOs as
  possible. U1 is at 0x27, clear of the CH224Q (0x22/0x23) and the
  ES9018K2M (0x48/0x49) on the same bus.
  - **Inputs:** P00-P05 are ENC_A, ENC_B, ENC_SW and BTN1-3. The TCA9535 has
    no internal pull-ups, so each input has a 10 k one.
  - **Outputs:** P10 is LCD_RST, with a 10 k pull-up so the LCD comes out of
    reset at power-up. P11-P13 drive the LED's red, green and blue.
  - **Unused:** P06, P07 and P14-P17 are pulled to GND together through R19.
    A floating input would keep firing INT, and the TCA9535 can't mask it.
- **The LCD socket J2 has contacts on both sides.** The panel lies on the
  board's top side, and its tail runs flat to J2 with the contacts facing up,
  so a bottom-contact socket would make no connection.
  - **Placement:** J2 sits 20.7 mm from the panel's left edge, matching the
    tail length on the datasheet drawing (page 10). Its pin 1 is at the top,
    on the tail's pin-1 side.
  - **Keepouts:** the area under the panel and the tail's path stay free of
    parts.
- **The backlight runs from +5V** through three 120 R resistors in parallel
  (40 R) and a low-side AO3400A.
  - **Current:** 39-61 mA over the supply and LED tolerances, 50 mA typical,
    against the datasheet's 80 mA.
  - **Why +5V:** the LEDs' 2.8-3.2 V leaves no headroom on 3.3 V.
  - **Why three resistors:** they keep each 0603 at 50 mW. A single 33 R 1206
    is not a JLC basic part.
- **The RGB LED is common anode on +5V,** because the green and blue dies
  need about 3 V. U1's pins are 5 V tolerant.
  - **Off, in firmware:** green and blue are driven high (3.3 V), and red is
    set as an input. 1.7 V could just light the red die.
  - **INT:** the interrupt handler ignores P11-P13.
- **The knob has no detents.** The EC11E1834403 is the cheapest EC11 with a
  push switch, and a smooth volume knob is normal on hi-fi. EC11E18244A5 is
  the detented drop-in on the same footprint.
- **The board is 110 x 40 mm**, against product.md's "about 100 x 40". The
  51.8 mm panel, its 20.7 mm tail and the 33 mm knob column don't fit in 100.
- **The LCD tail sets the left-end layout.** The panel sits at x 25.45 mm.
  - **Why there:** its 20.7 mm tail then ends at J2's insertion stop, 2.1 mm
    inside the socket mouth. The board reviewer measured the tail end
    within 0.08 mm of the stop, with a tolerance of +-0.5 mm.
  - **Tail shape:** the tail is about 20.5 mm wide for its first 10 mm, where
    it leaves the panel, and 6.5 mm wide where it enters J2. Both parts are
    keepouts, so no part sits under them and it lies flat.
  - **Moved for this:** the backlight parts and U1. The first board review
    caught the tail outline and the socket position, and both were fixed
    before routing (`reports/review-board.md`, then
    `reports/review-board-2.md`).
- **Routing:**
  - **Freerouting routes everything, GND included.** It runs before any pour
    exists, inside a 0.5 mm edge keepout. Without the keepout it ran tracks
    along the edge. It also doesn't know JLC's 0.5 mm hole-to-hole rule, so
    the default clearance is 0.2 mm, which keeps via holes 0.5 mm apart.
  - **GND vias:** each cap and IC GND pad then gets its own via.
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
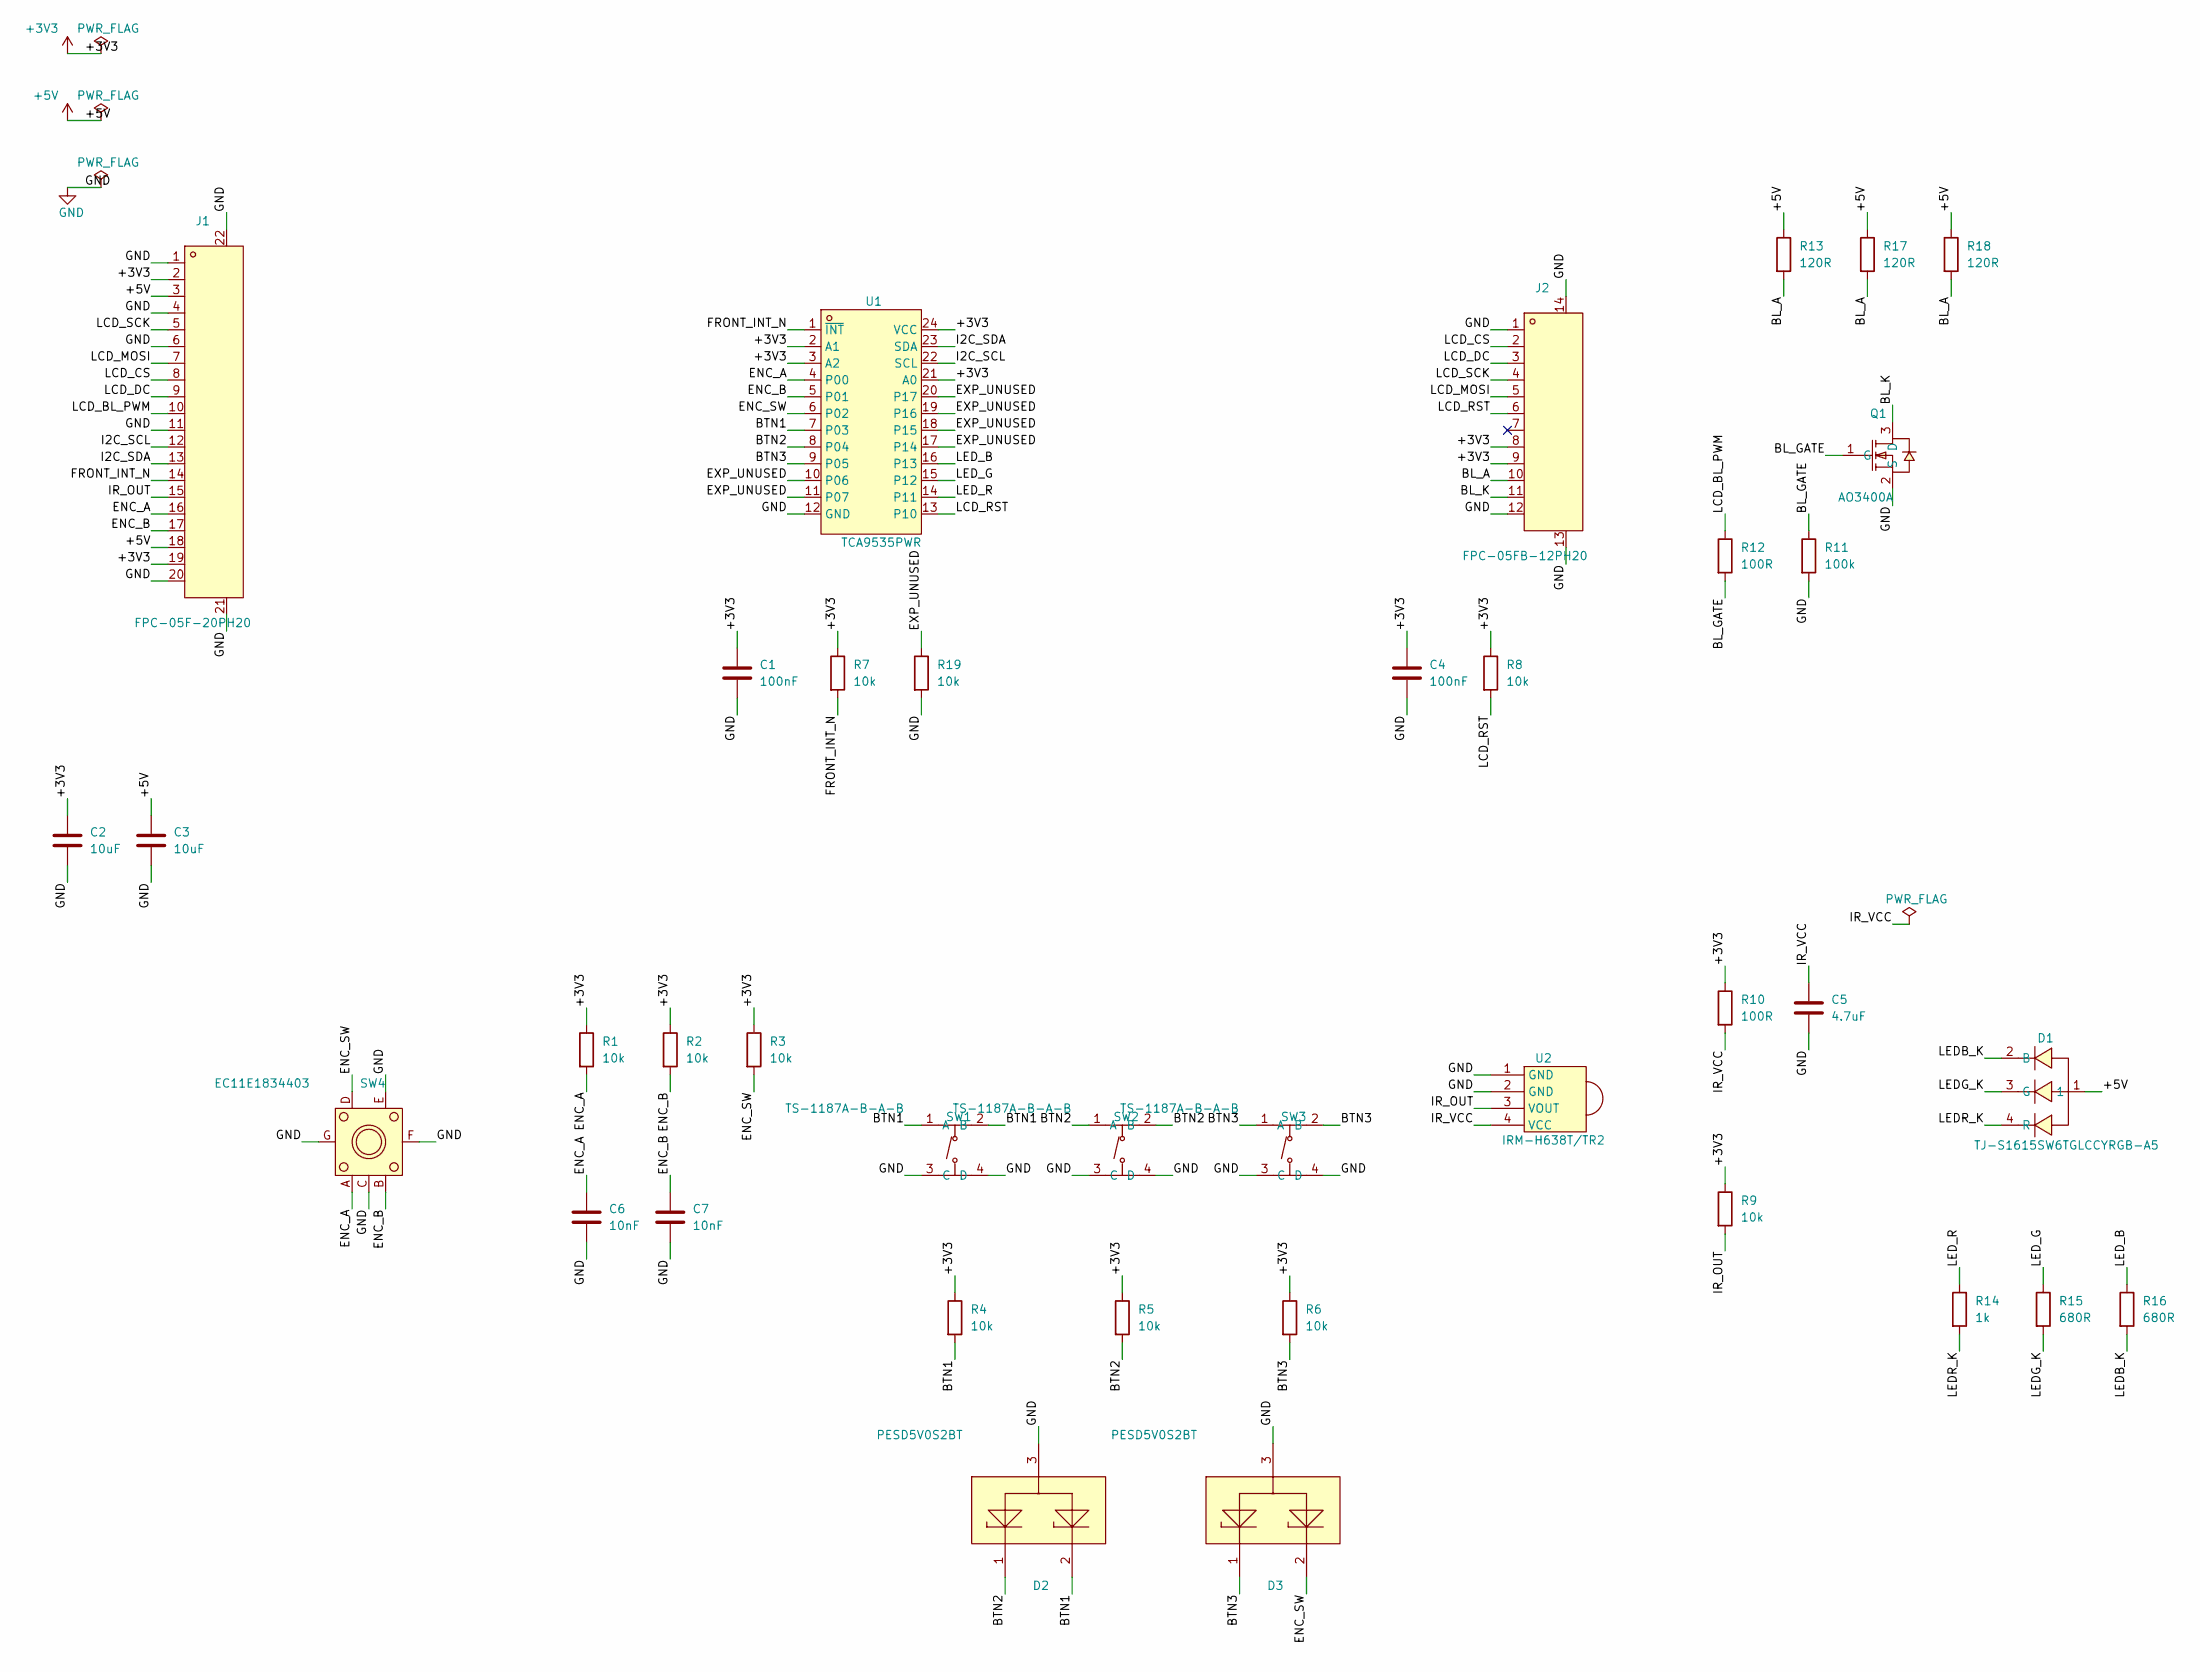
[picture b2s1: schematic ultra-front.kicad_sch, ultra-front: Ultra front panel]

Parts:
C1, C4: 100nF; C0603
C2, C3: 10uF; C0805
C5: 4.7uF; C0603
C6, C7: 10nF; C0603
D1: TJ-S1615SW6TGLCCYRGB-A5; LED-SMD_4P-L1.6-W1.5-TR
D2, D3: PESD5V0S2BT; SOT-23_L2.9-W1.3-P1.90-LS2.4-BR
J1: FPC-05F-20PH20; FPC-SMD_20P-P0.50_XUNPU_FPC-05F-20PH20
J2: FPC-05FB-12PH20; FPC-SMD_12P-P0.50_XUNPU_FPC-05FB-12PH20
Q1: AO3400A; SOT-23-3_L2.9-W1.3-P1.90-LS2.4-BR
R1, R2, R3, R4, R5, R6, R7, R8, R9, R19: 10k; R0603
R10, R12: 100R; R0603
R11: 100k; R0603
R13, R17, R18: 120R; R0603
R14: 1k; R0603
R15, R16: 680R; R0603
SW1, SW2, SW3: TS-1187A-B-A-B; SW-SMD_4P-L5.1-W5.1-P3.70-LS6.5-TL_H1.5
SW4: EC11E1834403; SW-TH_EC11E1820402
U1: TCA9535PWR; TSSOP-24_L7.8-W4.4-P0.65-LS6.4-BL
U2: IRM-H638T/TR2; SENSOR-SMD_IRM-H638T-TR2-TL

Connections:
+3V3: C1.1, C2.1, C4.1, J1.2, J1.19, J2.8, J2.9, R1.1, R2.1, R3.1, R4.1, R5.1, R6.1, R7.1, R8.1, R9.1, R10.1, U1.2 (A1), U1.3 (A2), U1.21 (A0), U1.24 (VCC)
+5V: C3.1, D1.1, J1.3, J1.18, R13.1, R17.1, R18.1
/BL_A: J2.10, R13.2, R17.2, R18.2
/BL_GATE: Q1.1 (G), R11.1, R12.2
/BL_K: J2.11, Q1.3 (D)
/BTN1: D2.2, R4.2, SW1.1 (A), SW1.2 (B), U1.7 (P03)
/BTN2: D2.1, R5.2, SW2.1 (A), SW2.2 (B), U1.8 (P04)
/BTN3: D3.1, R6.2, SW3.1 (A), SW3.2 (B), U1.9 (P05)
/ENC_A: C6.1, J1.16, R1.2, SW4.A, U1.4 (P00)
/ENC_B: C7.1, J1.17, R2.2, SW4.B, U1.5 (P01)
/ENC_SW: D3.2, R3.2, SW4.D, U1.6 (P02)
/EXP_UNUSED: R19.1, U1.10 (P06), U1.11 (P07), U1.17 (P14), U1.18 (P15), U1.19 (P16), U1.20 (P17)
/FRONT_INT_N: J1.14, R7.2, U1.1 (~INT)
/I2C_SCL: J1.12, U1.22 (SCL)
/I2C_SDA: J1.13, U1.23 (SDA)
/IR_OUT: J1.15, R9.2, U2.3 (VOUT)
/IR_VCC: C5.1, R10.2, U2.4 (VCC)
/LCD_BL_PWM: J1.10, R12.1
/LCD_CS: J1.8, J2.2
/LCD_DC: J1.9, J2.3
/LCD_MOSI: J1.7, J2.5
/LCD_RST: J2.6, R8.2, U1.13 (P10)
/LCD_SCK: J1.5, J2.4
/LEDB_K: D1.2 (B), R16.2
/LEDG_K: D1.3 (G), R15.2
/LEDR_K: D1.4 (R), R14.2
/LED_B: R16.1, U1.16 (P13)
/LED_G: R15.1, U1.15 (P12)
/LED_R: R14.1, U1.14 (P11)
GND: C1.2, C2.2, C3.2, C4.2, C5.2, C6.2, C7.2, D2.3, D3.3, J1.1, J1.4, J1.6, J1.11, J1.20, J1.21, J1.22, J2.1, J2.12, J2.13, J2.14, Q1.2 (S), R11.2, R19.2, SW1.3 (C), SW1.4 (D), SW2.3 (C), SW2.4 (D), SW3.3 (C), SW3.4 (D), SW4.C, SW4.E, SW4.F, SW4.G, U1.12 (GND), U2.1 (GND), U2.2 (GND); also elsewhere on the board

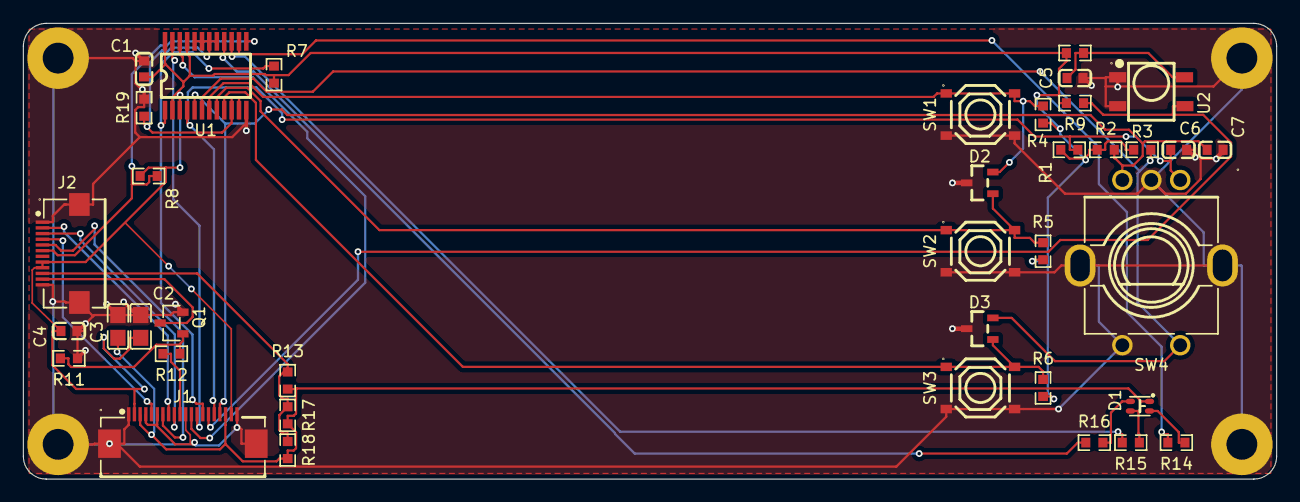
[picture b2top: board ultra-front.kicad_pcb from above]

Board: 2 copper layers, 110.0 x 40.0 mm, 42 parts (0 on the bottom side), 30 nets.

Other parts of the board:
H1, H2, H3, H4: MountingHole_2.7mm_M2.5_Pad

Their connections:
GND: H1.1, H2.1, H3.1, H4.1; also elsewhere on the board
